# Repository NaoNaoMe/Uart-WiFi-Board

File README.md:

Uart WiFi Board
=========

[  
*Uart WiFi Board(SKU-3849)*](https://international.switch-science.com/catalog/3849/)

## Uart WiFi Board has been launched! It is available in [the Switch Science store](https://international.switch-science.com/catalog/3849/).

The Uart WiFi Board designed as the transparent WiFi-serial bridge.  
There are some updates from the former Uart WiFi Board.  
 - The 128x32 pixels SSD1306 OLED display
 - The 3 user switches(a switch used as power switch too)

Thanks to add the 128x32 pixels OLED display, we can show IP address, SSID and Serial BaudRate.  
You don't need remember IP address and Baud Rate, you can see them in the display.
The Uart WiFi Board can be programmed using the Arduino IDE.

### Some highlights of the Uart WiFi Board:
 1. Main core: ESP-WROOM-02(ESP8266).
 2. Voltage regulator(3.3V) with control pin.
 3. Opto-isolated UART interface(Uart interface circuit accepts 3.3V and 5.0V).
 4. On board WiFi-controller can use following functions.
 	- LED1(IO2), SW1(IO12/POW_ON), SW2(IO16) and SW3(IO13)
 	- Control voltage regulator's control pin connected to "IO14" H:Enable L:Disable(normally)
 	- Voltage detection circuit(for CN1) connected to "TOUT"
 5. Measures 50mm x 60mm x 20mm

#### Some highlights of the Sample software:
 1. Totally transparent WiFi-serial bridge.
 2. IP address, SSID, Serial baud-rate and input-voltage can be displayed.
 3. Low voltage detection.
 
Sample software use the [esp8266-oled-ssd1306](https://github.com/ThingPulse/esp8266-oled-ssd1306) library.

Repository Contents
-------------------
* **/Hardware** - All Eagle design files (.brd, .sch)
* **/Software** - Software files for this hardware

Description(Pin Interfaces)
-------------------

### CN1(Primarily) Pin Descriptions:
This connector is the supply voltage.

| Pin | Name | Description                                                  |
| --- | ---- | ------------------------------------------------------------ |
| 1   | VBAT | Up to 12.0VDC convert to 3.3VDC                              |
| 2   | GND  | GND	                                                        |

### CN3(Primarily) Pin Descriptions:
This connector is for uploading software to WiFi-controller.  
To be selected BOOT MODE before supply voltage when you upload software.

| Pin | Name | Description                                                  |
| --- | ---- | ------------------------------------------------------------ |
| 1   | VCC  | 3.3VDC                                                       |
| 2   | TX   | UART TX	                                                    |
| 3   | RX   | UART RX	                                                    |
| 4   | GND  | GND	                                                        |
| 5   | BOOT | Connected to "IO0" H:Flash boot(normally) L:UART download    |

### CN2(Secondary) Pin Descriptions:
This connector is for your target board UART-interface.

| Pin | Name | Description                                                  |
| --- | ---- | ------------------------------------------------------------ |
| 1   | VIN  | 2.7VDC to 5.5VDC                                             |
| 2   | TX   | UART TX(Open collector output)	                            |
| 3   | RX   | UART RX	                                                    |
| 4   | GND  | GND	                                                        |

How to upload program
-------------------
See [this page](UploadProgram.md).

How to use the Uart WiFi Board
-------------------
An example is [here](Instructions.md).

License
-------------------
The repository is released under [Creative Commons ShareAlike 4.0 International](https://creativecommons.org/licenses/by-sa/4.0/).

Distributed as-is; no warranty is given.

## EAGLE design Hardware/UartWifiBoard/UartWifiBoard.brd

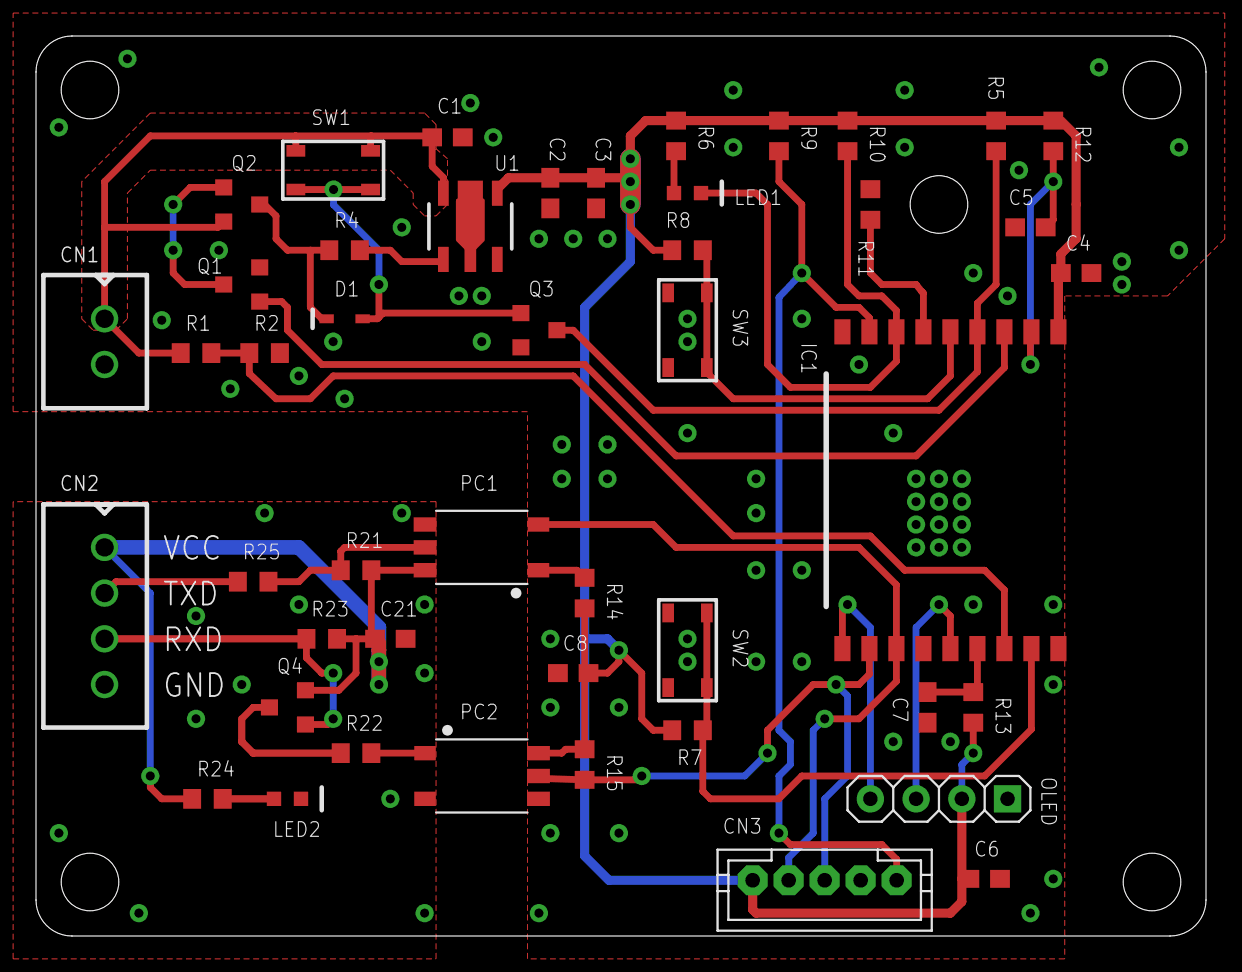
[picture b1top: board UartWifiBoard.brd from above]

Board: 2 copper layers, 65.0 x 50.0 mm, 46 parts (0 on the bottom side), 31 nets.

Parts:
C1: 1.0u; C0603
C2, C3: 2.2u; C0603
C4, C5, C6, C7, C8, C21: 0.1u; C0603
CN1: B2B-XH
CN2: B4B-XH
CN3: B5B-PH
D1: RB521S30; SOD-523F
IC1: ESP-WROOM-02
LED1: OSOR1608C1A; LED0603SMD
LED2: OSHR1608C1A; LED0603SMD
OLED1: DISPLAY-OLED-128X32
PC1, PC2: TLP2368; SO6-5PIN
Q1, Q3: MMUN2211LT1G; SOT-23
Q2, Q4: MMUN2111LT1G; SOT-23
R1, R12: 10.0k; R0603
R2, R15: 1.0k; R0603
R4, R25: 220; R0603
R5, R6, R7, R8, R9, R10, R11, R13, R23: 3.3k; R0603
R14, R22: 470; R0603
R21, R24: 4.7k; R0603
SW1, SW2, SW3: SKRPACE010; SKRP
U1: NJM2884U1; SOT89-5

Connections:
IO0: CN3.5, IC1.8, R9.1
IO2: IC1.7, LED1.C, R10.1
IO4: IC1.10, OLED1.4
IO5: IC1.14, OLED1.3
IO12: IC1.4, Q3.P$3, R5.1
IO13: IC1.5, R8.1, SW3.1, SW3.2
IO14: IC1.3, Q1.P$1
IO15: IC1.6, R11.2
IO16: IC1.17, R7.1, SW2.1, SW2.2
unnamed: Q1.P$3, Q2.P$1
unnamed: R4.2, U1.1
unnamed: C1.1, CN1.1, Q2.P$2, R1.2, SW1.1, SW1.2, U1.6
unnamed: Q4.P$3, R22.2
unnamed: D1.C, Q2.P$3, R4.1
unnamed: CN2.3, Q4.P$1, R23.1
unnamed: PC2.1, R22.1
unnamed: PC1.5, R21.1, R25.2
unnamed: CN2.2, R25.1
unnamed: LED2.A, R24.1
unnamed: D1.A, Q3.P$1, SW1.3, SW1.4
unnamed: PC1.1, R14.1
unnamed: C5.1, IC1.2, R12.1
unnamed: LED1.A, R6.1
P+3V3: C2.1, C3.1, C4.1, C6.1, C8.1, CN3.1, IC1.1, OLED1.2, PC2.6, R5.2, R6.2, R7.2, R8.2, R9.2, R10.2, R12.2, R13.2, R14.2, R15.2, U1.4
PGND: C1.2, C2.2, C3.2, C4.2, C5.2, C6.2, C7.2, C8.2, CN1.2, CN3.4, IC1.9, IC1.13, IC1.18, OLED1.1, PC2.4, Q1.P$2, Q3.P$2, R2.1, R11.1, SW2.3, SW2.4, SW3.3, SW3.4, U1.2, U1.5
RST: C7.1, IC1.15, R13.1
RXD: CN3.3, IC1.11, PC2.5, R15.1
S+SUP: C21.1, CN2.1, PC1.6, Q4.P$2, R21.2, R23.2, R24.2
SGND: C21.2, CN2.4, LED2.C, PC1.4, PC2.3
TOUT: IC1.16, R1.1, R2.2
TXD: CN3.2, IC1.12, PC1.3

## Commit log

2017-03-31 add files
2017-04-08 update files
2018-04-18 Upload files
2018-04-18 Upload new files
2018-04-18 Fix some mistakes
2018-04-18 Fix alignment of pictures
2018-04-20 Update instruction
2018-04-20 add gif image
2018-04-25 Add calibrating

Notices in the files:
parts and their libraries:
jst: Copyright (C) 2016, Naoya Imai
generic-brand-oled-modules: Copyright (C) 2017, Naoya Imai
